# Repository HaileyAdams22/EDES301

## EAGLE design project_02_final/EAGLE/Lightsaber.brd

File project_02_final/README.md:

# Lightsaber PCB
EDES301 Lightsaber Project 2 - PCB Design

The files in this repository outline the PCB (printed circuit board) designed and generated using Eagle. Included are pdf files of the schematic, top and bottom layers of the board, gerber files for all layers of the board, a bill of materials, and a mechanical block diagram. All files necessary for manufacturing can be found here.

The pdfs can be used to see the schematic and overall design of the board.
The gerber files can be used for manufacturing the board.
The bill of materials can also be used for manufacturing the board.
The mecanical block diagram can be used for understanding the measurements of the board.

This PCB was designed with the help and direction of Erik Welsh.

The EAGLE folder contains the library, schematic, and layout files for Eagle as well as all gerber files. The DOCS folder contains some screenshots as well as some background info.

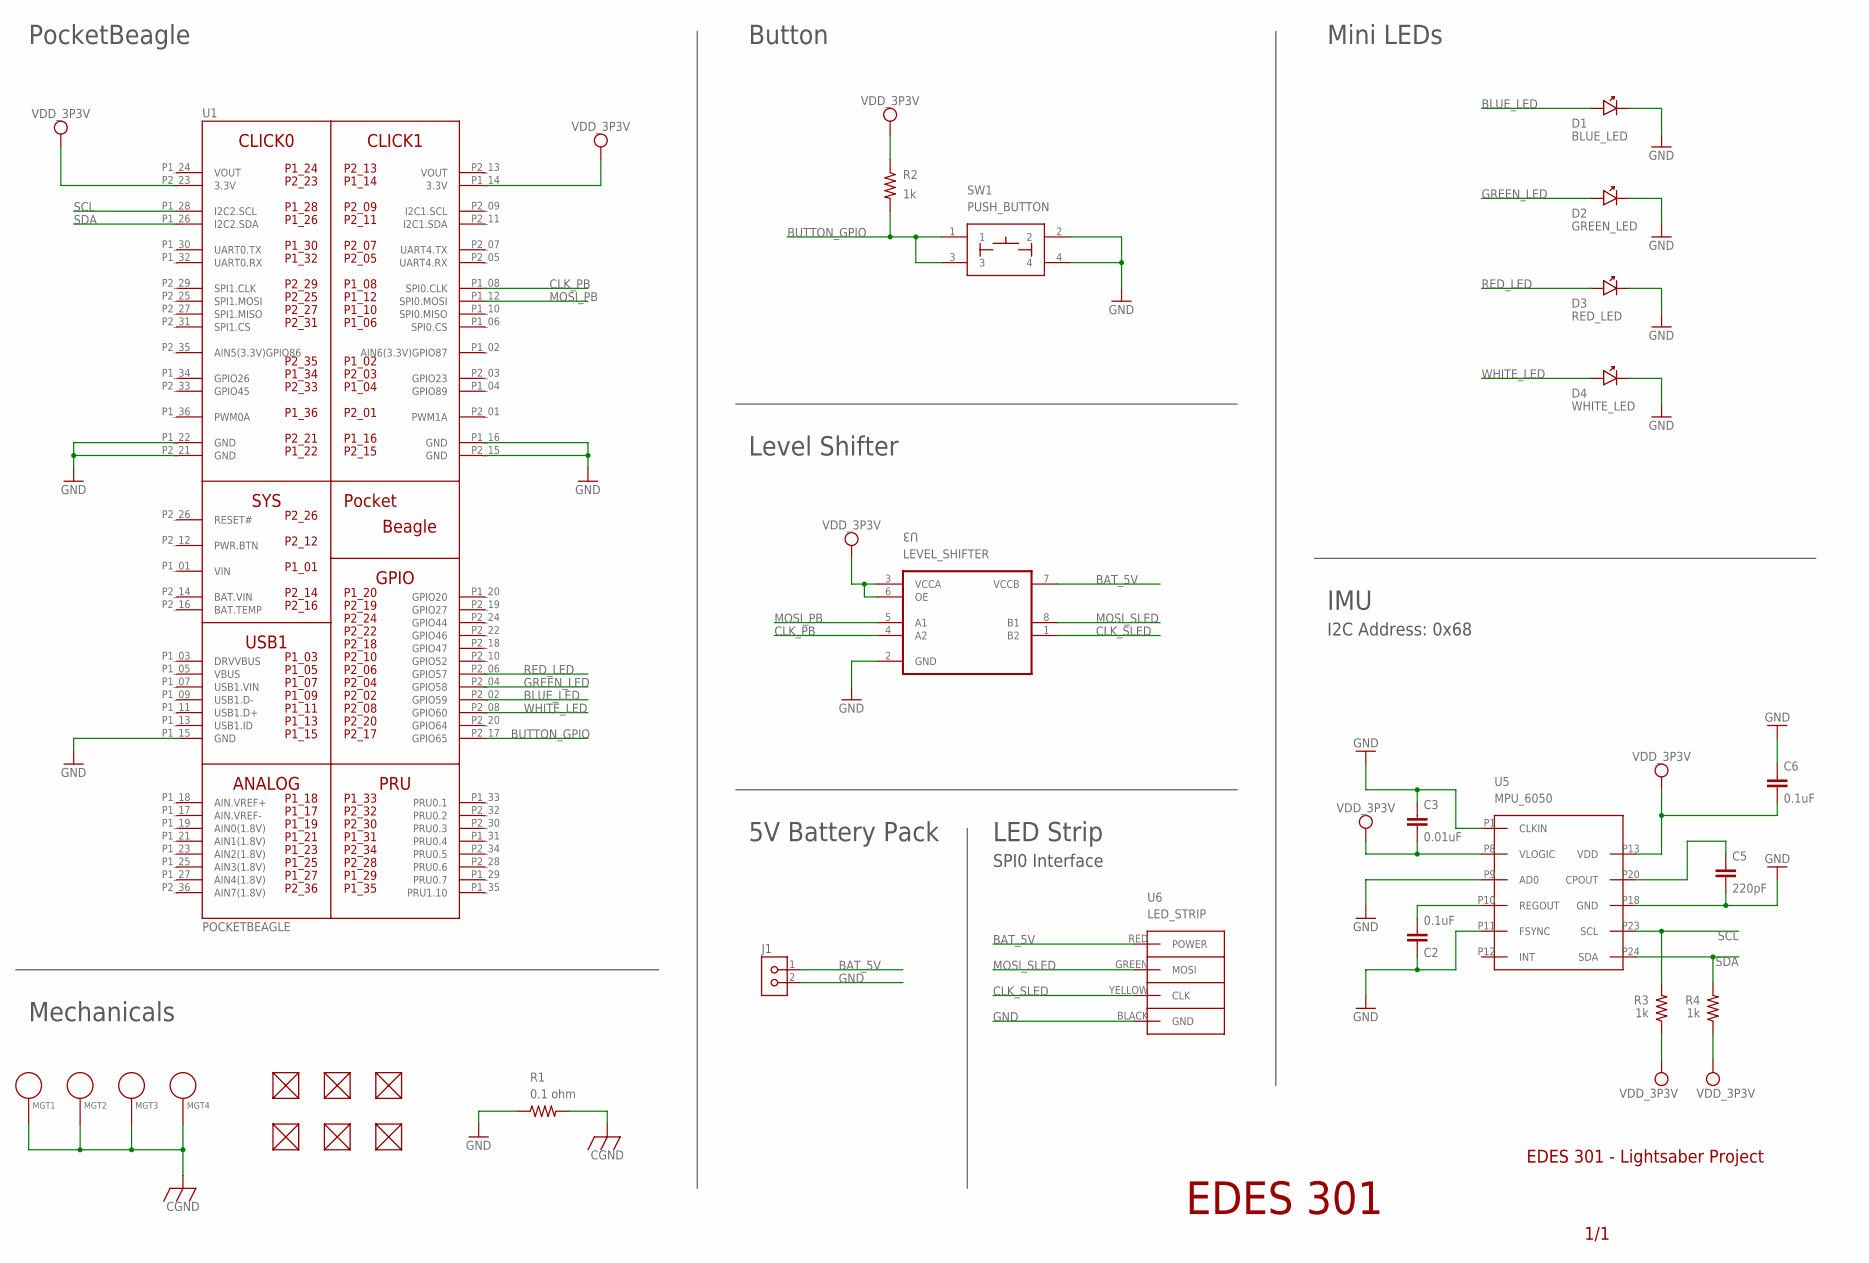
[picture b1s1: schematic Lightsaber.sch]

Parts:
C2, C6: 0.1uF; C0603
C3: 0.01uF; C0603
C5: 220pF; C0603
D1: BLUE_LED; LED
D2: GREEN_LED; LED
D3: RED_LED; LED
D4: WHITE_LED; LED
FUD1, FUD2, FUD3, FUD4, FUD5, FUD6: FIDUCIAL; FIDUCIAL_40MIL
J1: PINHD-1X2; H1X2-2.54
MGT1, MGT2, MGT3, MGT4: MOUNTING_HOLE
R1: 0.1 ohm; R0805
R2, R3, R4: 1k; R0603
SW1: PUSH_BUTTON; BUTTON_12.5MM
U1: POCKETBEAGLE
U3: LEVEL_SHIFTER
U5: MPU_6050
U6: LED_STRIP

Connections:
BAT.VIN: U1.P2_14 (BAT.VIN)
BAT_5V: J1.1, U3.7 (VCCB), U6.RED (POWER)
BLUE_LED: D1.ANODE, U1.P2_02 (GPIO59)
BUTTON_GPIO: R2.2, SW1.1, SW1.3, U1.P2_17 (GPIO65)
CGND: MGT1.P$1, MGT2.P$1, MGT3.P$1, MGT4.P$1, R1.2
CLK_PB: U1.P1_08 (SPI0.CLK), U3.4 (A2)
CLK_SLED: U3.1 (B2), U6.YELLOW (CLK)
GND: C2.2, C3.1, C5.2, C6.1, D1.CATHODE, D2.CATHODE, D3.CATHODE, D4.CATHODE, J1.2, R1.1, SW1.2, SW1.4, U1.P1_15 (GND), U1.P1_16 (GND), U1.P1_22 (GND), U1.P2_15 (GND), U1.P2_21 (GND), U3.2 (GND), U5.P1 (CLKIN), U5.P9 (AD0), U5.P11 (FSYNC), U5.P18 (GND), U6.BLACK (GND)
GREEN_LED: D2.ANODE, U1.P2_04 (GPIO58)
MOSI_PB: U1.P1_12 (SPI0.MOSI), U3.5 (A1)
MOSI_SLED: U3.8 (B1), U6.GREEN (MOSI)
unnamed: C2.1, U5.P10 (REGOUT)
unnamed: C5.1, U5.P20 (CPOUT)
RED_LED: D3.ANODE, U1.P2_06 (GPIO57)
SCL: R3.2, U1.P1_28 (I2C2.SCL), U5.P23 (SCL)
SDA: R4.2, U1.P1_26 (I2C2.SDA), U5.P24 (SDA)
VDD_3P3V: C3.2, C6.2, R2.1, R3.1, R4.1, U1.P1_14 (3.3V), U1.P2_23 (3.3V), U3.3 (VCCA), U3.6 (OE), U5.P8 (VLOGIC), U5.P13 (VDD)
VIN: U1.P1_01 (VIN)
VOUT: U1.P1_24 (VOUT), U1.P2_13 (VOUT)
WHITE_LED: D4.ANODE, U1.P2_08 (GPIO60)

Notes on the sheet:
PocketBeagle
Button
Level Shifter
LED Strip
IMU
Mini LEDs
I2C Address: 0x68
SPI0 Interface
1/1
EDES 301 - Lightsaber Project
EDES 301
Mechanicals
5V Battery Pack

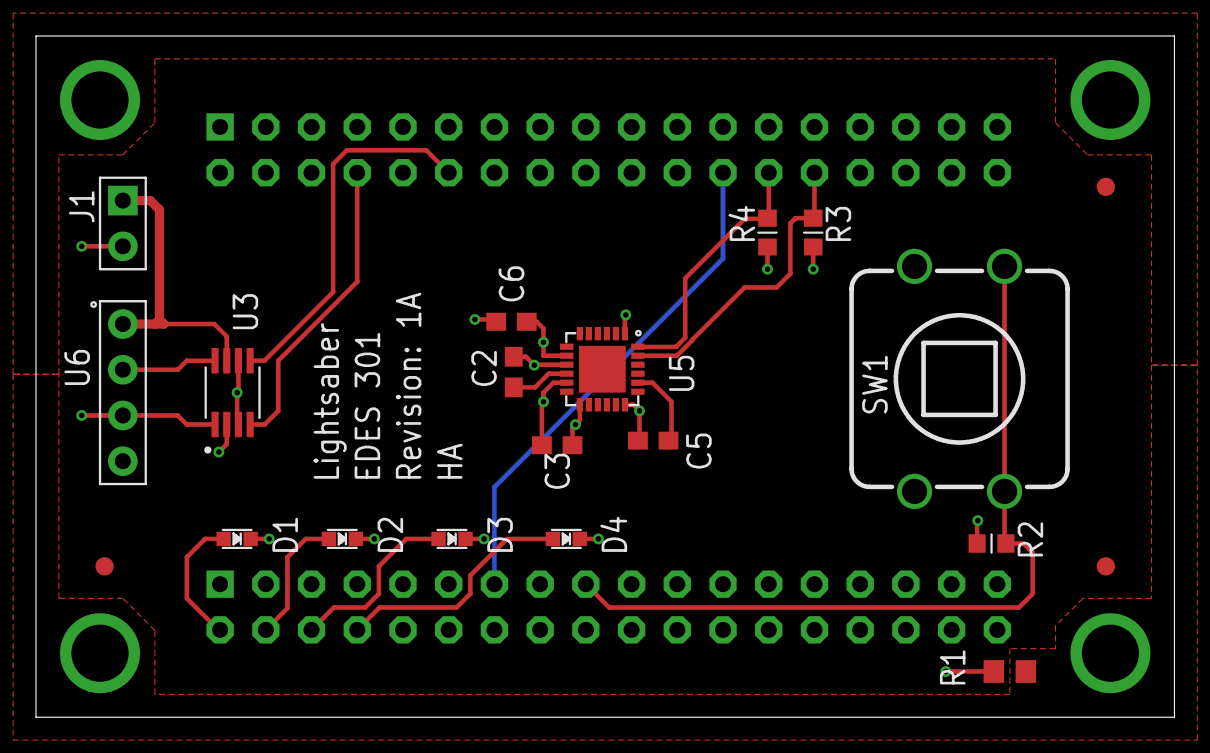
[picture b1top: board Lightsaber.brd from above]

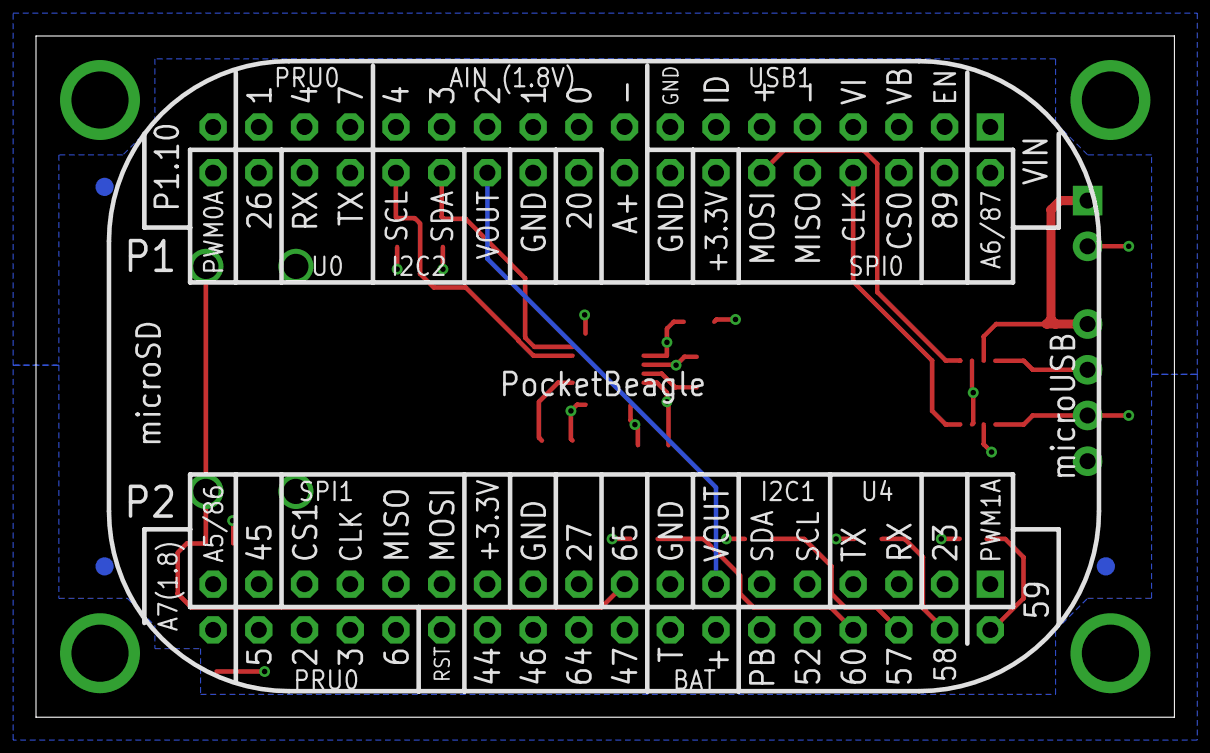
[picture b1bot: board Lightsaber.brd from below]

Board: 4 copper layers, 63.2 x 37.8 mm, 28 parts (4 on the bottom side), 18 nets.

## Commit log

2025-02-16 Assignment 4 simple_calc
2025-02-16 Assignment 4 blink_USR3 LED at 5 Hz
2025-02-16 Assignemnt 4 button
2025-04-17 Add sLED_test
2025-04-19 IMU, LED, button tests and outlines for project
2025-04-19 Threaded Button File
2025-04-19 sLED Test Code Updates
2025-04-19 More sLED Updates
2025-04-19 Driver Edits and light_saber.py
2025-04-19 Driver updates and light_saber.py
2025-04-20 light_up and light_down animations
2025-04-24 sLED and mLED and button connection
2025-04-24 finished Light Saber Code
2025-04-25 run and configure scrips
2025-04-26 Final Commit
2025-05-06 Rename Bottom Layer.pdf to project_02/Bottom Layer.pdf
2025-05-06 Rename Lightsaber.csv to project_02/Lightsaber.csv
2025-05-06 Rename Schematic.pdf to project_02/Schematic.pdf
2025-05-06 Rename Top Layer.pdf to project_02/Top Layer.pdf
2025-05-06 Rename copper_bottom_l4.gbr to project_02/copper_bottom_l4.gbr
2025-05-06 Rename copper_inner_l2.gbr to project_02/copper_inner_l2.gbr
2025-05-06 Rename copper_inner_l3.gbr to project_02/copper_inner_l3.gbr
2025-05-06 Rename copper_top_l1.gbr to project_02/copper_top_l1.gbr
2025-05-06 Rename gerber_job.gbrjob to project_02/gerber_job.gbrjob
2025-05-06 Rename profile.gbr to project_02/profile.gbr
2025-05-06 Rename silkscreen_bottom.gbr to project_02/silkscreen_bottom.gbr
2025-05-06 Rename silkscreen_top.gbr to project_02/silkscreen_top.gbr
2025-05-06 Rename soldermask_bottom.gbr to project_02/soldermask_bottom.gbr
2025-05-06 Rename soldermask_top.gbr to project_02/soldermask_top.gbr
2025-05-06 Rename solderpaste_bottom.gbr to project_02/solderpaste_bottom.gbr
2025-05-06 Rename solderpaste_top.gbr to project_02/solderpaste_top.gbr
2025-05-06 Create EAGLE
2025-05-06 Create MFG-CAM
2025-05-06 Rename project_02_final/EAGLE/copper_bottom_l4.gbr to project_02_final/EAGLE/MFG-CAM/copper_bottom_l4.gbr
2025-05-06 Rename project_02_final/EAGLE/copper_inner_l2.gbr to project_02_final/EAGLE/MFG-CAM/copper_inner_l2.gbr
2025-05-07 Rename project_02_final/EAGLE/copper_inner_l3.gbr to project_02_final/EAGLE/MFG-CAM/copper_inner_l3.gbr
2025-05-07 Rename project_02_final/EAGLE/copper_top_l1.gbr to project_02_final/EAGLE/MFG-CAM/copper_top_l1.gbr
2025-05-07 Rename project_02_final/EAGLE/gerber_job.gbrjob to project_02_final/EAGLE/MFG-CAM/gerber_job.gbrjob
2025-05-07 Rename project_02_final/EAGLE/profile.gbr to project_02_final/EAGLE/MFG-CAM/profile.gbr
2025-05-07 Rename project_02_final/EAGLE/silkscreen_bottom.gbr to project_02_final/EAGLE/MFG-CAM/silkscreen_bottom.gbr
2025-05-07 Rename project_02_final/EAGLE/silkscreen_top.gbr to project_02_final/EAGLE/MFG-CAM/silkscreen_top.gbr
2025-05-07 Rename project_02_final/EAGLE/soldermask_bottom.gbr to project_02_final/EAGLE/MFG-CAM/soldermask_bottom.gbr
2025-05-07 Rename project_02_final/EAGLE/soldermask_top.gbr to project_02_final/EAGLE/MFG-CAM/soldermask_top.gbr
2025-05-07 Rename project_02_final/EAGLE/solderpaste_bottom.gbr to project_02_final/EAGLE/MFG-CAM/solderpaste_bottom.gbr
2025-05-07 Rename project_02_final/EAGLE/solderpaste_top.gbr to project_02_final/EAGLE/MFG-CAM/solderpaste_top.gbr
2025-05-07 Rename project_02_final/EAGLE/Lightsaber.txt to project_02_final/EAGLE/MFG-CAM/Lightsaber.txt
2025-05-07 Rename project_02_final/EAGLE/drill_1_16.xln to project_02_final/EAGLE/MFG-CAM/drill_1_16.xln
2025-05-07 Rename README.md to temp.md
